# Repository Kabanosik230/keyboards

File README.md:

# Hackpad

My 3x3 macropad project for Hack Club Stardance. It features 9 MX switches, a 0.91" OLED display, and a rotary encoder, powered by a Seeed Studio XIAO RP2040.

## Hardware / BOM
* Seeed Studio XIAO RP2040
* 9x Cherry MX style switches + keycaps
* 0.91" I2C OLED display (SSD1306)
* EC11 Rotary encoder + knob
* Custom PCB
* 3D printed case (top & bottom)
* M3 screws

## Project Structure
* `cad/` - 3D case model (.step)
* `pcb/` - KiCad PCB files (.kicad_sch, .kicad_pcb)
* `keyboards/hackpad/` - QMK firmware setup

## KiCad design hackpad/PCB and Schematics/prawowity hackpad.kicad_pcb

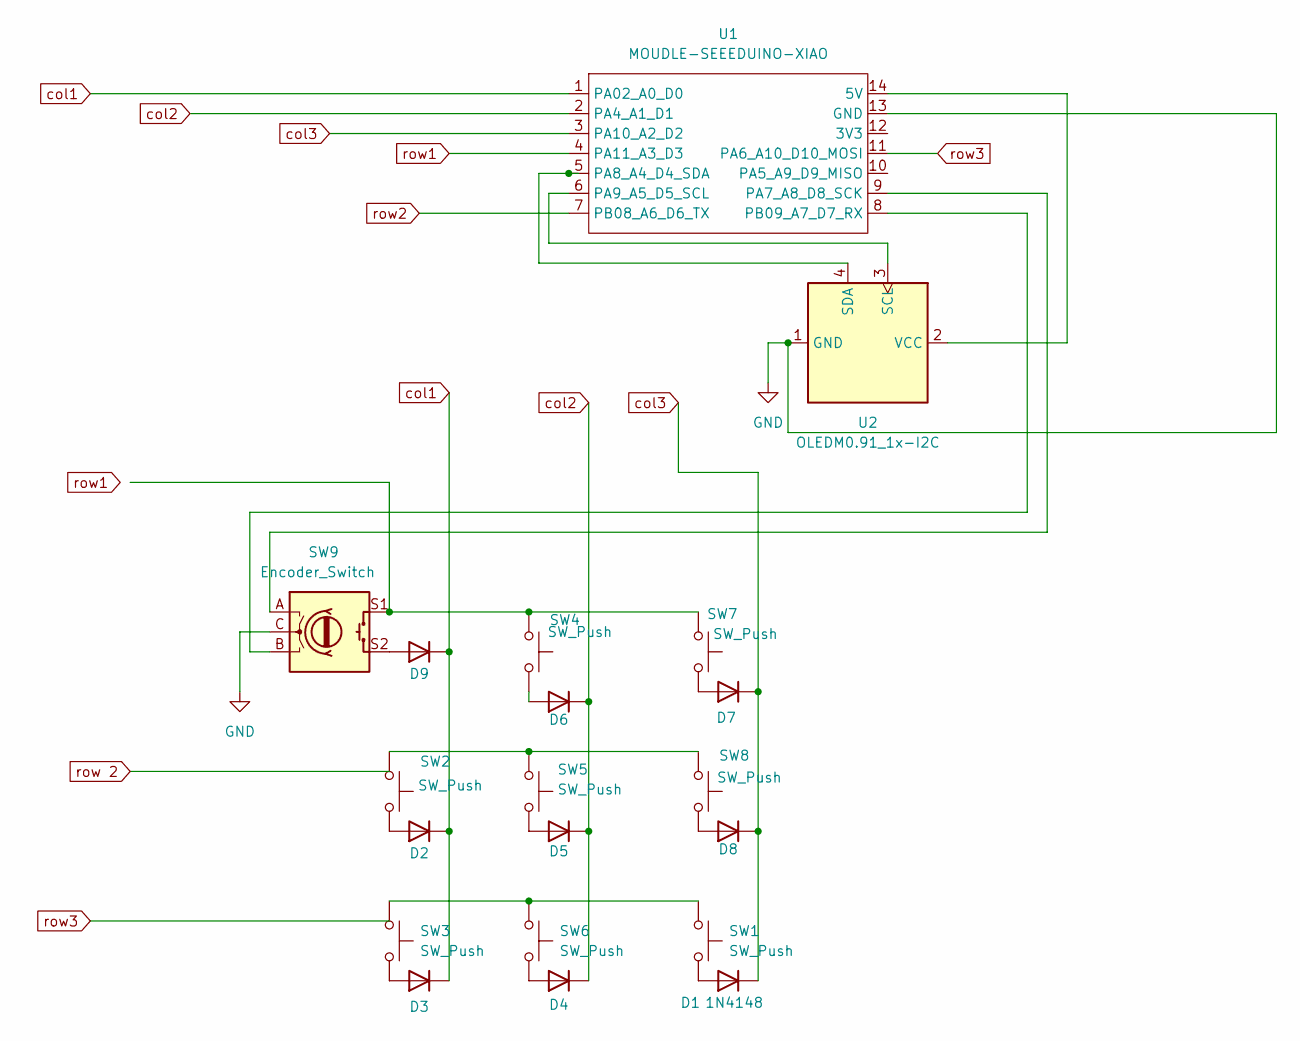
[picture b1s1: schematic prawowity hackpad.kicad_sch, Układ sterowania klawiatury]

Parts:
D1, D2, D3, D4, D5, D6, D7, D8, D9: 1N4148; D_DO-35_SOD27_P7.62mm_Horizontal
SW1, SW2, SW3, SW4, SW5, SW6, SW7, SW8: SW_Push; SW_Cherry_MX_1.00u_PCB
SW9: Encoder_Switch; RotaryEncoder_Alps_EC11E-Switch_Vertical_H20mm_MountingHoles
U1: MOUDLE-SEEEDUINO-XIAO; XIAO-Generic-Hybrid-14P-2.54-21X17.8MM
U2: OLEDM0.91_1x-I2C; ER_OLEDM0.91_1x-I2C

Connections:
GND: SW9.C, U1.13 (GND), U2.1 (GND)
unnamed: D1.2 (A), SW1.2
unnamed: D2.2 (A), SW2.2
unnamed: D3.2 (A), SW3.2
unnamed: D4.2 (A), SW6.2
unnamed: D5.2 (A), SW5.2
unnamed: D6.2 (A), SW4.2
unnamed: D7.2 (A), SW7.2
unnamed: D8.2 (A), SW8.2
unnamed: D9.2 (A), SW9.S2
unnamed: SW1.1, SW3.1, SW6.1
unnamed: SW2.1, SW5.1, SW8.1
unnamed: SW4.1, SW7.1, SW9.S1
unnamed: U1.14 (5V), U2.2 (VCC)
unnamed: SW9.A, U1.9 (PA7_A8_D8_SCK)
unnamed: U1.5 (PA8_A4_D4_SDA), U2.4 (SDA)
unnamed: U1.6 (PA9_A5_D5_SCL), U2.3 (SCL)
unnamed: SW9.B, U1.8 (PB09_A7_D7_RX)
col1: D2.1 (K), D3.1 (K), D9.1 (K), U1.1 (PA02_A0_D0)
col2: D4.1 (K), D5.1 (K), D6.1 (K), U1.2 (PA4_A1_D1)
col3: D1.1 (K), D7.1 (K), D8.1 (K), U1.3 (PA10_A2_D2)
row1: U1.4 (PA11_A3_D3)
row2: U1.7 (PB08_A6_D6_TX)
row3: U1.11 (PA6_A10_D10_MOSI)

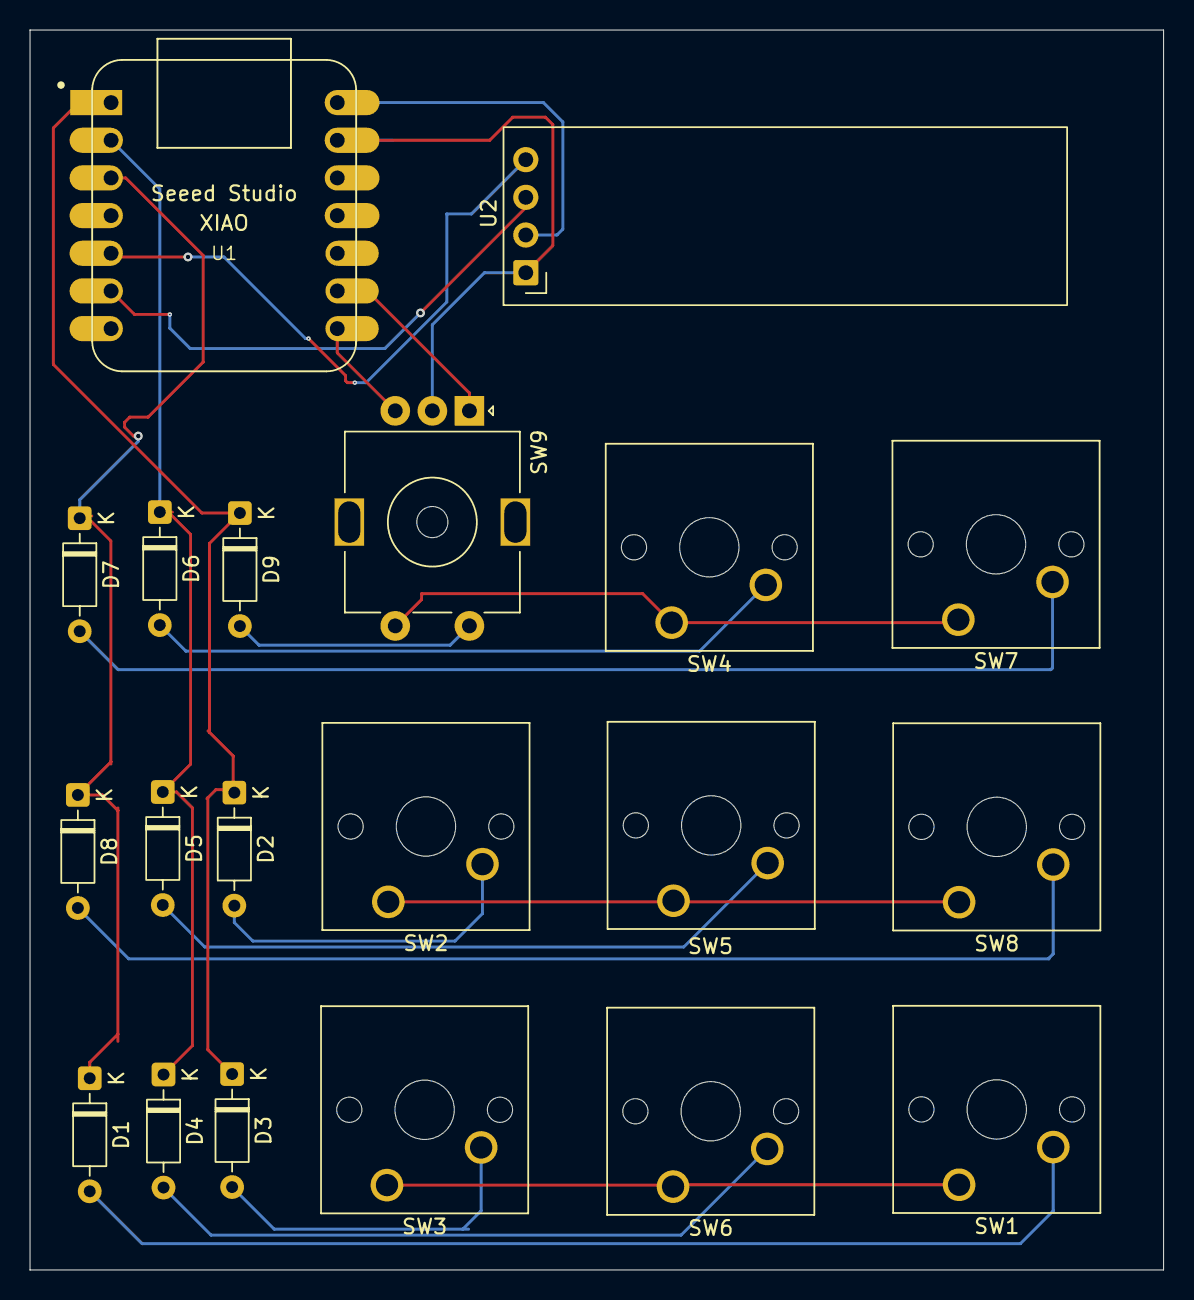
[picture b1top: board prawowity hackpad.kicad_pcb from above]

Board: 2 copper layers, 76.4 x 83.6 mm, 20 parts (0 on the bottom side), 21 nets.
